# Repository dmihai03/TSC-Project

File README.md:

# eBook reader - Pacuraru Mihai Dorin

This product is an eBook reader that uses an **ESP32-C6** microcontroller powered by an **USB Type-C**.

 Implementation steps:
    - create 2D schematic
    - create 2D PCB, solving routing errors
    - add 3D model to every component 
    - pushed 2D PCB to 3D
    - created 3D model for battery
    - imported display model
    - build the final 3D model of product

---

## Block Diagram

---

## Hardware functionalities

### ESP32-C6 microcontroller

The ESP32-C6 microcontroller has a single core SoC RISC-V that supports:
  - WiFi6, Bluetooth 5, Zigbee and Thread
  - integrated flash memory up to 8 MB
  - 23 GPIO pins
  - SPI, 12C, UART, I2S, USB interfaces support

Charging and energy management:
  - USB-C that uses USB4110-GF-A connector with ESD protection for battery charging
  - LiPo battery that gets charged with the help of MCP73831 controller
  - the integrated circuit MAX17048G+T10 for monitorizing battery charging level via I2C interface

Display system:
  - E-Paper driver interface connected to microcontroller via SPI

Memory:
  - microSD card interface connected via SPI for heavy data

Buttons:
  - BOOT -> the microcontroller enters in bootloader
  - RESET -> general reset
  - I/O CHANGE -> user I/O interactions

### ESP32-C6 pins configuration
| Component | PIN |
|----|----|
|Display SPI | MOSI, CLK, CS, DC |
|BME688 | SDA, SCL, I2C |
|Buttons | GPIO1, GPIO2, GPIO3 |
|USB-C | D+, D-, VBUS |

---
## Bill of Materials (BOM)
| Component | Buy | Datasheet |
| ---------- | --------- | --------- |
| PFMF.050.1 | [Retailer](https://ro.mouser.com/ProductDetail/Schurter/PFMF.050.2?qs=1auRipcfynCums5v1iucSA%3D%3D) |  [Datasheet](https://ro.mouser.com/datasheet/2/358/typ_PFMF-1275918.pdf) |
| USB4110-GF-A | [Retailer](https://ro.mouser.com/ProductDetail/GCT/USB4110-GF-A?qs=KUoIvG%2F9IlYiZvIXQjyJeA%3D%3D) | [Datasheet](https://ro.mouser.com/datasheet/2/837/GCT_USB4110_Product_Drawing___20k_cycles-3455479.pdf) |
| USBLC6-2SC6Y | [Retailer](https://ro.mouser.com/ProductDetail/STMicroelectronics/USBLC6-2SC6Y?qs=gNDSiZmRJS%2FOgDexvXkdow%3D%3D) | [Datasheet](https://ro.mouser.com/datasheet/2/389/usblc6_2sc6y-1852505.pdf) |
| SD0805S020S1R0 | [Retailer](https://ro.mouser.com/ProductDetail/KYOCERA-AVX/SD0805S020S1R0?qs=jCA%252BPfw4LHbpkAoSnwrdjw%3D%3D) | [Datasheet](https://ro.mouser.com/datasheet/2/40/schottky-3165252.pdf) |
| DMG2305UX-7 | [Retailer](https://ro.mouser.com/ProductDetail/Diodes-Incorporated/DMG2305UX-7?qs=L1DZKBg7t5F%2FNBHrjfxC%252Bg%3D%3D) | [Datasheet](https://www.diodes.com/assets/Datasheets/DMG2305UX.pdf) |
| XC6220A331MR-G | [Retailer](https://ro.mouser.com/ProductDetail/Torex-Semiconductor/XC6220A331MR-G?qs=AsjdqWjXhJ8ZSWznL1J0gg%3D%3D) | [Datasheet](https://ro.mouser.com/datasheet/2/760/xc6220-3371556.pdf) |
| Condensator 100 uF TANT | [Retailer](https://ro.mouser.com/ProductDetail/KYOCERA-AVX/TAJW107M010RNJ?qs=Wtp%252Bf%2FAeVqIH8v1VxV%252B1Rg%3D%3D) | [Datasheet](https://ro.mouser.com/datasheet/2/40/TAJ-3165264.pdf) |
| 112A-TAAR-R03_ATTEND | [Retailer](https://www.digikey.ro/en/products/detail/attend-technology/112A-TAAR-R03/17633923) | [Datasheet](https://www.attend.com.tw/data/download/file/112A-TAAR-R03_Spec.pdf)
| ESP32-C6-WROOM-1-N8 | [Retailer](https://ro.mouser.com/ProductDetail/Espressif-Systems/ESP32-C6-WROOM-1-N8?qs=8Wlm6%252BaMh8ST02Gmwp74cw%3D%3D) | [Datasheet](https://ro.mouser.com/datasheet/2/891/Espressif_ESP32_C6_WROOM_1__Datasheet_V0_1_PRELIMI-3239987.pdf) |
| MCP73831 | [Retailer](https://ro.mouser.com/ProductDetail/Microchip-Technology/MCP73831T-2ACI-OT?qs=yUQqVecv4qvbBQBGbHx0Mw%3D%3D) | [Datasheet](https://ro.mouser.com/datasheet/2/268/MCP73831_Family_Data_Sheet_DS20001984H-3441711.pdf) |
| CHG_LED | [Retailer](https://store.comet.srl.ro/Catalogue/Product/40478/) | [Datasheet](https://www.snapeda.com/parts/KP-1608SURCK/Kingbright/datasheet/) |
| SI1308EDL-T1-GE3 | [Retailer](https://ro.mouser.com/ProductDetail/Vishay-Semiconductors/SI1308EDL-T1-GE3?qs=bX1%252BNvsK%2FBramh9tgpOaEw%3D%3D) | [Datasheet](https://www.vishay.com/doc?63399) |
| MBR0530 | [Retailer](https://ro.mouser.com/ProductDetail/Micro-Commercial-Components-MCC/MBR0530-T?qs=9VyI4qLX4NTSXkb9ynzJnA%3D%3D) | [Datasheet](https://ro.mouser.com/datasheet/2/258/mcc_mbr0520~mbr0560sod123-1179695.pdf) |
| L1 | [Retailer](https://ro.mouser.com/ProductDetail/Wurth-Elektronik/744043680?qs=PGXP4M47uW6VkZq%252BkzjrHA%3D%3D) | [Datasheet](https://www.we-online.com/components/products/datasheet/744043680.pdf) |
| FH34SRJ-24S-0.5SH_99_ | [Retailer](https://ro.mouser.com/ProductDetail/Hirose-Connector/FH34SRJ-24S-0.5SH99?qs=vcbW%252B4%252BSTIpKBl5ap9J8Fw%3D%3D) | [Datasheet](https://ro.mouser.com/datasheet/2/185/FH34SRJ_24S_0_5SH_99__CL0580_1255_6_99_2DDrawing_0-1615044.pdf) |
| BME688 | [Retailer](https://ro.mouser.com/ProductDetail/Bosch-Sensortec/BME688?qs=IS%252B4QmGtzzqQoVDscqwx3A%3D%3D) | [Datasheet](https://ro.mouser.com/datasheet/2/783/bst_bme688_fl000-2307034.pdf) |
| BD5229G-TR | [Retailer](https://ro.mouser.com/ProductDetail/ROHM-Semiconductor/BD5229G-TR?qs=4kLU8WoGk0vvnhrrYwdszw%3D%3D) | [Datasheet](https://fscdn.rohm.com/en/products/databook/datasheet/ic/power/voltage_detector/bd52xxg-e.pdf) |
| Button | [Retailer](https://ro.mouser.com/ProductDetail/CK/KMR221GULCLFS?qs=u2NJ%252B70r0goBXaNk7IrU0Q%3D%3D) | [Datasheet](https://www.ckswitches.com/media/1479/kmr2.pdf) |
| MAX17048G+T10 | [Retailer](https://ro.mouser.com/ProductDetail/Analog-Devices-Maxim-Integrated/MAX17048G%2bT10?qs=D7PJwyCwLAoGnnn8jEPRBQ%3D%3D) | [Datasheet](https://ro.mouser.com/datasheet/2/609/MAX17048_MAX17049-3469099.pdf) |
| W25Q512JVEIQ | [Retailer](https://ro.mouser.com/ProductDetail/Winbond/W25Q512JVEIQ?qs=l7cgNqFNU1jw6svr3at6tA%3D%3D) | [Datasheet](https://ro.mouser.com/datasheet/2/949/Winbond_W25Q512JV_Datasheet-3240039.pdf) |
| PGB1010603MR | [Retailer](https://ro.mouser.com/ProductDetail/Littelfuse/PGB1010603MRHF?qs=KvZd0dN2Zg%2FuIq6icj%252BGKA%3D%3D) | [Datasheet](https://www.littelfuse.com/media?resourcetype=datasheets&itemid=8a337998-d54d-466b-be4e-dc5bcd1f9321&filename=littelfuse_pulseguard_pgb1_datasheet.pdf) |
| QWIIC_RIGHT_ANGLE | [Retailer](https://ro.mouser.com/ProductDetail/GCT/USB4110-GF-A?qs=KUoIvG%2F9IlYiZvIXQjyJeA%3D%3D) | [Datasheet](https://ro.mouser.com/datasheet/2/837/GCT_USB4110_Product_Drawing___20k_cycles-3455479.pdf) |
| DS3231SN# | [Retailer](https://ro.mouser.com/ProductDetail/Analog-Devices-Maxim-Integrated/DS3231SN?qs=ffX8NcjNb2RmKAb9wAk9Ug%3D%3D) | [Datasheet](https://ro.mouser.com/datasheet/2/609/DS3231-3421123.pdf) |
| CPH3225A C10_SUPERCAP | [Retailer](https://ro.mouser.com/ProductDetail/Seiko-Semiconductors/CPH3225A?qs=3etwrb1wR%252BhUOph6lAO7eg%3D%3D) | [Datasheet](https://ro.mouser.com/datasheet/2/360/Seiko_Instruments_MicroBattery_E_20230330_2024Jan_-3561061.pdf) |
| Condensator 100nF | [Retailer](https://ro.mouser.com/ProductDetail/KYOCERA-AVX/06033G104ZAT2A?qs=NXubJDmysXJMPmHfVo6Z%252BA%3D%3D) | [Datasheet](https://ro.mouser.com/datasheet/2/40/KGM_Y5V-3223189.pdf) |
| Condensator 4.7uF | [Retailer](https://ro.mouser.com/ProductDetail/KYOCERA-AVX/0402ZD475MAT2A?qs=NBFAU1oqP4W4U2PCPHI0sg%3D%3D) | [Datasheet](https://ro.mouser.com/datasheet/2/40/cx5r_KGM-3223198.pdf) |
| Condensator 10uF | [Retailer](https://ro.mouser.com/ProductDetail/Samsung-Electro-Mechanics/CL10A106KQ8NNNL?qs=xZ%2FP%252Ba9zWqaes9JKSsob2Q%3D%3D) | [Datasheet](https://ro.mouser.com/datasheet/2/585/MLCC-1837944.pdf) |
| Condensator 1uF/50V | [Retailer](https://ro.mouser.com/ProductDetail/KYOCERA-AVX/06035D105MAT2A?qs=k4kUdCzLgS5%252BURKe1SOIeQ%3D%3D) | [Datasheet](https://ro.mouser.com/datasheet/2/40/cx5r_KGM-3223198.pdf) |
| Resistor 10K | [Retailer](https://ro.mouser.com/ProductDetail/Vishay-Beyschlag/MCS0402MD1002BE000?qs=17u8i%2FzlE8%2F9BrAaXkMk1w%3D%3D) | [Datasheet](https://www.vishay.com/doc?28952) |
| Resistor 200 | [Retailer](https://ro.mouser.com/ProductDetail/Vishay-Beyschlag/MCS0402MD2000BE100?qs=3SvaY9RawMJNVte4F12%252BZQ%3D%3D) | [Datasheet](https://www.vishay.com/doc?28952) |
| Resistor 100K | [Retailer](https://ro.mouser.com/ProductDetail/Vishay-Beyschlag/MCT0603PD1003DP500?qs=5aG0NVq1C4wWAn8Ei3OpZA%3D%3D) | [Datasheet](https://www.vishay.com/doc?28916) |
| Resistor 2.2 | [Retailer](https://ro.mouser.com/ProductDetail/SEI-Stackpole/RMCF0402FT2R20?qs=IPgv5n7u5QbBgyl0jwhwsA%3D%3D) | [Datasheet](https://ro.mouser.com/datasheet/2/385/SEI_RMCF_RMCP-3077565.pdf) |
| Resistor 5K1| [Retailer](https://www.venkel.com/part/TFCR0603-16W-K-5690FT) | [Datasheet](https://data.venkel.com/documents/tfcr-series?_gl=1*tdo8m*_ga*NTA1MTc5MTcyLjE3NDM4OTMzNjc.*_ga_JRKGBZNVM8*MTc0Mzg5MzM2Ni4xLjAuMTc0Mzg5MzM2OC41OC4wLjA.) |
| Resistor 2K | [Retailer](https://ro.mouser.com/ProductDetail/Vishay-Beyschlag/MCS04020C2001FE000?qs=wTZ%2FFzl837YG0wIkZJJOwQ%3D%3D) | [Datasheet](https://www.vishay.com/doc?28705) |
| Resistor 0.47 | [Retailer](https://ro.mouser.com/ProductDetail/SEI-Stackpole/CSR0402JKR470?qs=IPgv5n7u5QawIB6nBEt8wA%3D%3D) | [Datasheet](https://ro.mouser.com/datasheet/2/385/SEI_CSR_CSRN-3077593.pdf) |
| Resistor 15 | [Retailer](https://ro.mouser.com/ProductDetail/YAGEO/RT0402FRE0715RL?qs=BXCcY9r%252B08DFFpLSkPOIqQ%3D%3D) | [Datasheet](https://ro.mouser.com/datasheet/2/447/PYu_RT_1_to_0_01_RoHS_L_15-3461507.pdf) |

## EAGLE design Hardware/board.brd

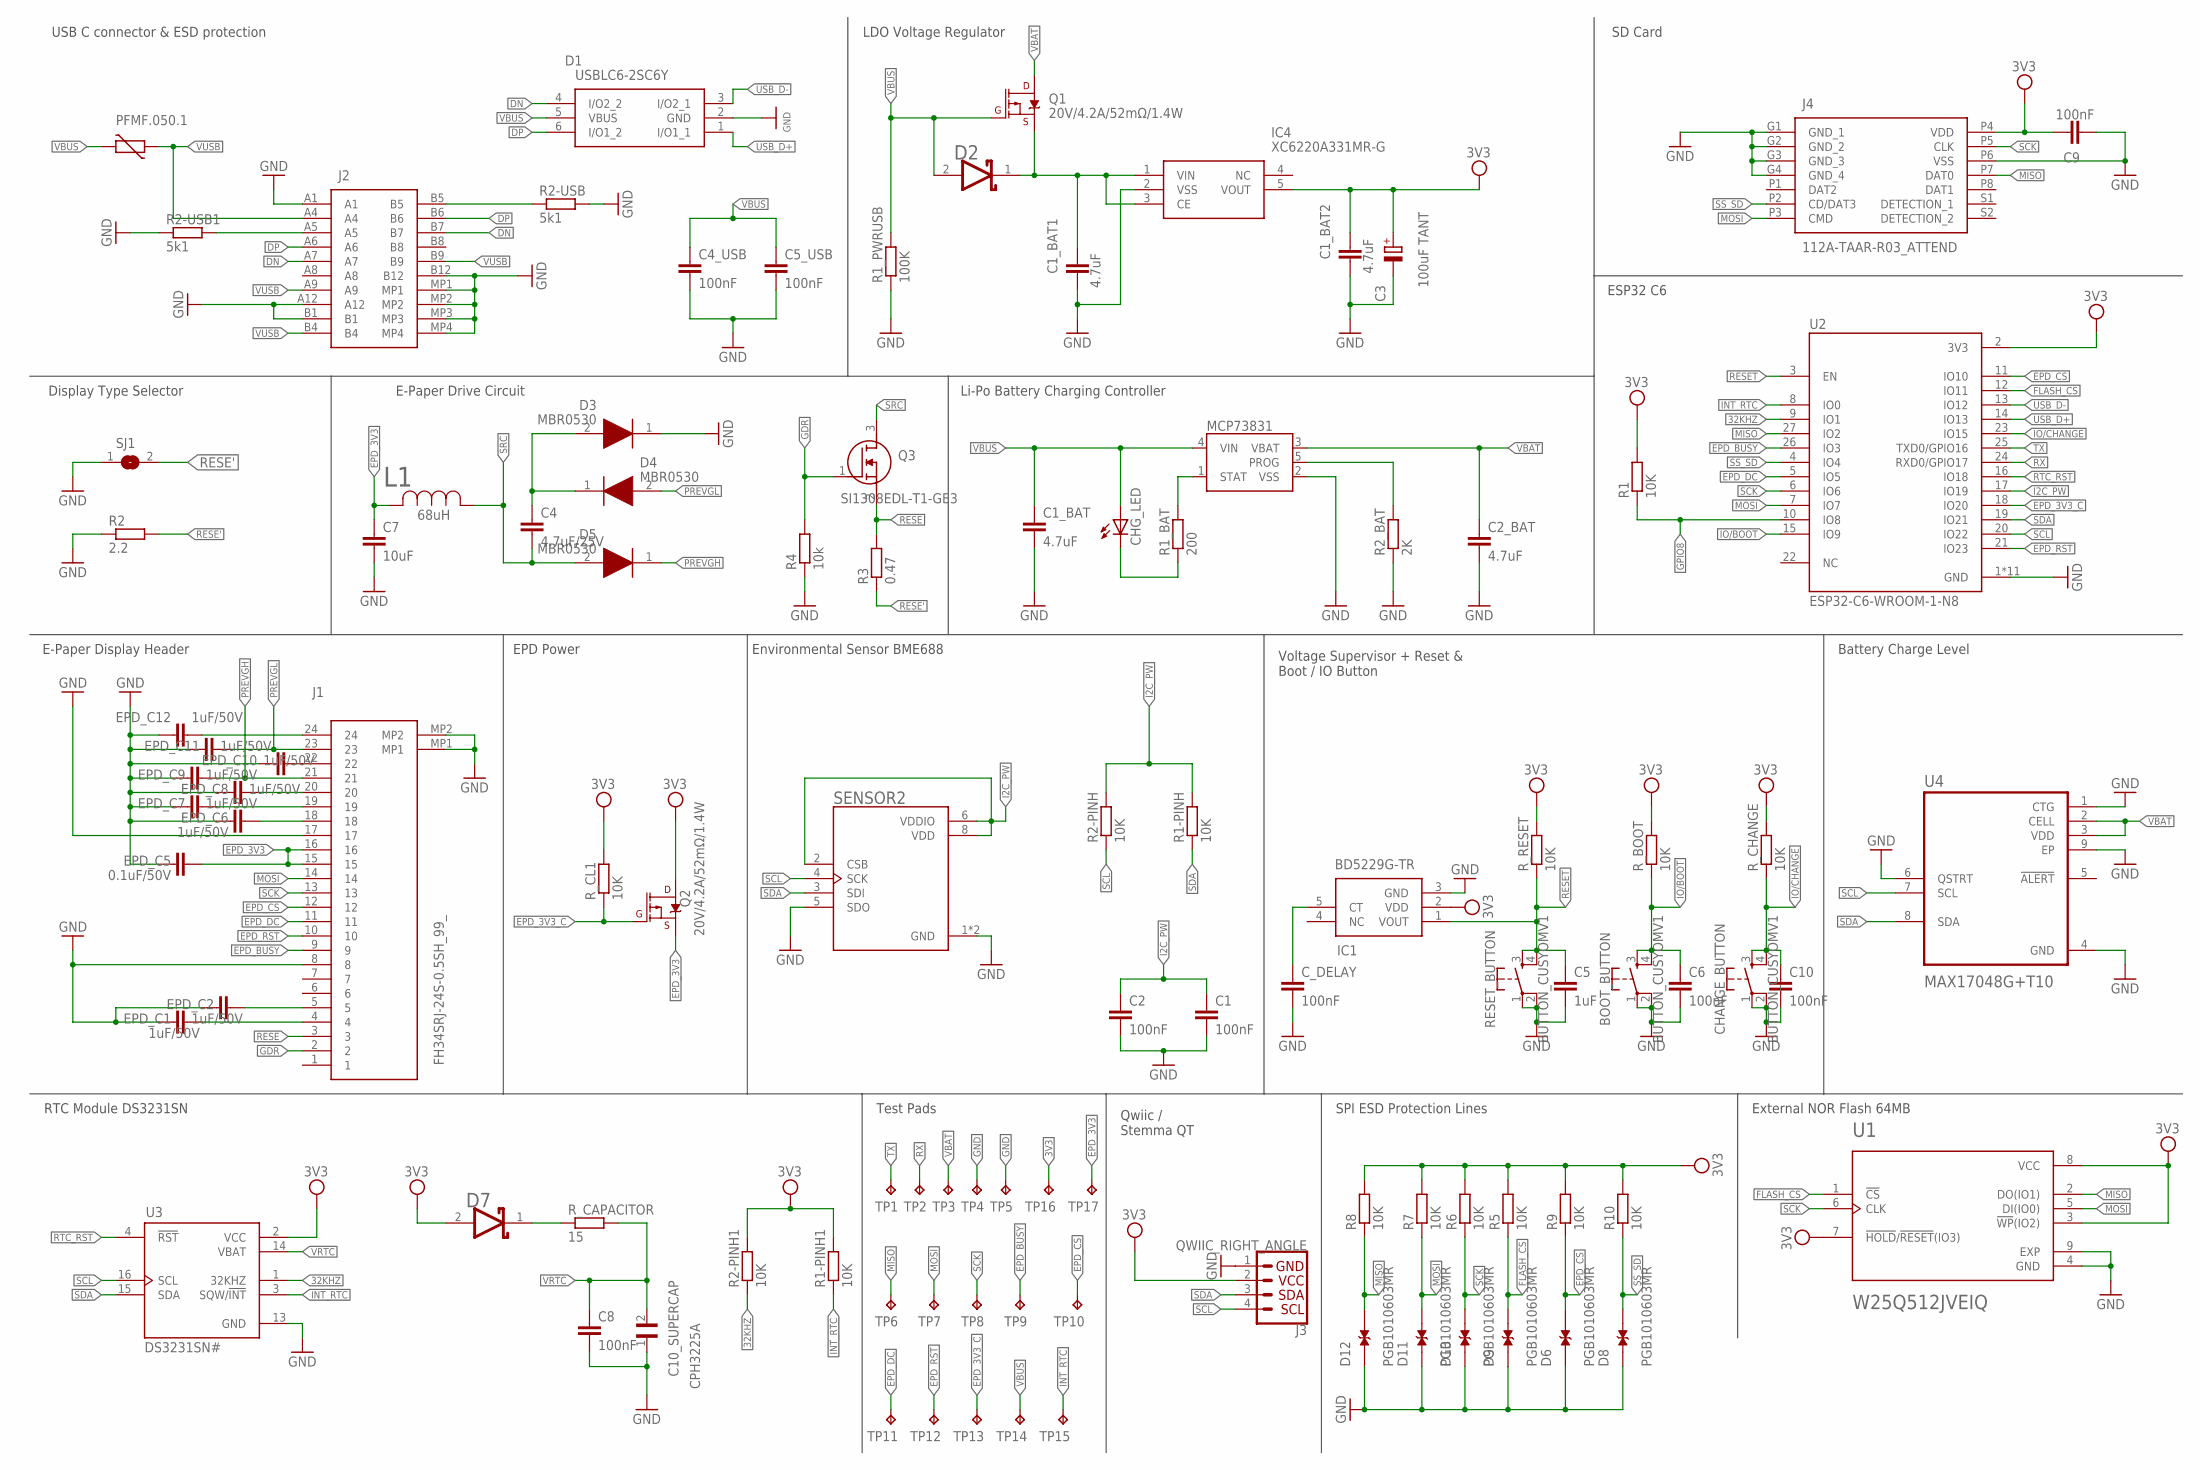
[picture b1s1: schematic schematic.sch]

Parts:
BOOT_BUTTON: BUTTON_CUSYOMV1; MYBUTTON
C1, C2, C4_USB, C5_USB, C6, C8, C9, C10: 100nF; ESP32_WROVER_EAGLE-LTSPICE_C0402
C1_BAT, C1_BAT1, C1_BAT2, C2_BAT: 4.7uF; ESP32_WROVER_EAGLE-LTSPICE_C0402
C3: 100uF TANT; RCL_CT3528
C4: 4.7uF/25V; ESP32_WROVER_EAGLE-LTSPICE_C0402
C5: 1uF; ESP32_WROVER_EAGLE-LTSPICE_C0402
C7: 10uF; ESP32_WROVER_EAGLE-LTSPICE_C0402
C10_SUPERCAP: CPH3225A; CAPCP3225X100N
CHANGE_BUTTON: BUTTON_CUSYOMV1; MYBUTTON
CHG_LED: ADAFRUIT_LEDCHIP-LED0603; ADAFRUIT_CHIP-LED0603
C_DELAY: 100nF; ESP32_WROVER_EAGLE-LTSPICE_C0402
D1: USBLC6-2SC6Y; SOT95P280X145-6N
D2, D7: ESP32_WROVER_AVX---SD0805S020S1R0_AVX_SD0805S020S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; ESP32_WROVER_AVX---SD0805S020S1R0_AVX_SD0805S020S1R0_0
D3, D4, D5: MBR0530; SOD3716X135N
D6, D8, D9, D10, D11, D12: PGB1010603MR; DIOC1608X36N
EPD_C1, EPD_C2, EPD_C6, EPD_C7, EPD_C8, EPD_C9, EPD_C10, EPD_C11, EPD_C12: 1uF/50V; ESP32_WROVER_EAGLE-LTSPICE_C0402
EPD_C5: 0.1uF/50V; ESP32_WROVER_EAGLE-LTSPICE_C0402
IC1: BD5229G-TR; SOT95P280X125-5N
IC4: XC6220A331MR-G; SOT95P280X120-5N
J1: FH34SRJ-24S-0.5SH_99_; FH34SRJ24S05SH99
J2: SAMACSYS_PARTS_USB4110-GF-A; SAMACSYS_PARTS_USB4110GFA
J3: QWIIC_RIGHT_ANGLE; JST04_1MM_RA
J4: 112A-TAAR-R03_ATTEND; 112ATAARR03ATTEND
L1: 744043680IND_4828-WE-TPC_WRE; IND_4828-WE-TPC_WRE
MCP73831: ESP32_WROVER_SPARKFUN-IC-POWER_MCP73831; ESP32_WROVER_SPARKFUN-IC-POWER_SOT23-5
PFMF.050.1: ESP32C6_VARISTORCN1812; ESP32C6_VARISTOR_CT/CN1812
Q1, Q2: 20V/4.2A/52mΩ/1.4W; ESP32_WROVER_SPARKFUN-DISCRETESEMI_SOT23-3
Q3: SI1308EDL-T1-GE3; SOT65P210X110-3N
R1, R1-PINH, R1-PINH1, R2-PINH, R2-PINH1, R5, R6, R7, R8, R9, R10: 10K; ESP32_WROVER_EAGLE-LTSPICE_R0402
R1_BAT: 200; ESP32_WROVER_EAGLE-LTSPICE_R0402
R1_PWRUSB: 100K; ESP32_WROVER_EAGLE-LTSPICE_R0402
R2: 2.2; ESP32_WROVER_EAGLE-LTSPICE_R0402
R2-USB, R2-USB1: 5k1; ESP32_WROVER_EAGLE-LTSPICE_R0402
R2_BAT: 2K; ESP32_WROVER_EAGLE-LTSPICE_R0402
R3: 0.47; ESP32_WROVER_EAGLE-LTSPICE_R0402
R4: 10k; ESP32_WROVER_EAGLE-LTSPICE_R0402
RESET_BUTTON: BUTTON_CUSYOMV1; MYBUTTON
R_BOOT: 10K; ESP32_WROVER_EAGLE-LTSPICE_R0402
R_CAPACITOR: 15; ESP32_WROVER_EAGLE-LTSPICE_R0402
R_CHANGE: 10K; ESP32_WROVER_EAGLE-LTSPICE_R0402
R_CL1: 10K; ESP32_WROVER_EAGLE-LTSPICE_R0402
R_RESET: 10K; ESP32_WROVER_EAGLE-LTSPICE_R0402
SENSOR2: ESP32_WROVER_BME680_BME680; ESP32_WROVER_BME680_PSON80P300X300X100-8N
SJ1: SJ
TP1, TP2, TP3, TP4, TP5, TP6, TP7, TP8, TP9, TP10, TP11, TP12, TP13, TP14, TP15, TP16, TP17: TPTP20R; TP20R
U1: W25Q512JVEIQ; SON127P600X800X80-9N
U2: ESP32-C6-WROOM-1-N8; XCVR_ESP32-C6-WROOM-1-N8
U3: DS3231SN#; SOIC127P1032X265-16N
U4: MAX17048G+T10; SON50P200X200X80-9N

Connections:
3V3: C1_BAT2.1, C3.+, C9.1, D7.2 (ANODE), IC1.2 (VDD), IC4.5 (VOUT), J3.2, J4.P4 (VDD), Q2.3 (D), R1.2, R1-PINH1.2, R2-PINH1.2, R5.2, R6.2, R7.2, R8.2, R9.2, R10.2, R_BOOT.2, R_CHANGE.2, R_CL1.2, R_RESET.2, TP16.TP, U1.3 (!WP!(IO2)), U1.7 (!HOLD!/!RESET!(IO3)), U1.8 (VCC), U2.2 (3V3), U3.2 (VCC)
32KHZ: R2-PINH1.1, U2.9 (IO1), U3.1 (32KHZ)
DN: D1.4 (I/O2_2), J2.A7, J2.B7
DP: D1.6 (I/O1_2), J2.A6, J2.B6
EPD_3V3: C7.1, EPD_C5.2, J1.15, J1.16, L1.2, Q2.2 (S), TP17.TP
EPD_3V3_C: Q2.1 (G), R_CL1.1, TP13.TP, U2.18 (IO20)
EPD_BUSY: J1.9, TP9.TP, U2.26 (IO3)
EPD_CS: D6.2, J1.12, R9.1, TP10.TP, U2.11 (IO10)
EPD_DC: J1.11, TP11.TP, U2.5 (IO5)
EPD_RST: J1.10, TP12.TP, U2.21 (IO23)
FLASH_CS: D9.2, R5.1, U1.1 (!CS), U2.12 (IO11)
GDR: J1.2, Q3.1 (G), R4.2
GND: BOOT_BUTTON.1, BOOT_BUTTON.2, C1.2, C1_BAT.2, C1_BAT1.2, C1_BAT2.2, C2.2, C2_BAT.2, C3.-, C4_USB.2, C5.2, C5_USB.2, C6.2, C7.2, C8.2, C9.2, C10.2, C10_SUPERCAP.1, CHANGE_BUTTON.1, CHANGE_BUTTON.2, C_DELAY.2, D1.2 (GND), D3.1 (K), D6.1, D8.1, D9.1, D10.1, D11.1, D12.1, EPD_C1.1, EPD_C2.1, EPD_C5.1, EPD_C6.1, EPD_C7.1, EPD_C8.1, EPD_C9.1, EPD_C10.1, EPD_C11.1, EPD_C12.1, IC1.3 (GND), IC4.2 (VSS), J1.8, J1.17, J1.MP1, J1.MP2, J2.A1, J2.A12, J2.B1, J2.B12, J2.MP1, J2.MP2, J2.MP3, J2.MP4, J3.1, J4.G1 (GND_1), J4.G2 (GND_2), J4.G3 (GND_3), J4.G4 (GND_4), J4.P6 (VSS), MCP73831.2 (VSS), R1_PWRUSB.1, R2.1, R2-USB.2, R2-USB1.1, R2_BAT.1, R4.1, RESET_BUTTON.1, RESET_BUTTON.2, SENSOR2.1 (GND), SENSOR2.5 (SDO), SENSOR2.7 (GND), SJ1.1, TP4.TP, TP5.TP, U1.4 (GND), U1.9 (EXP), U2.1 (GND), U2.28 (GND), U2.29_1 (GND), U2.29_2 (GND), U2.29_3 (GND), U2.29_4 (GND), U2.29_5 (GND), U2.29_6 (GND), U2.29_7 (GND), U2.29_8 (GND), U2.29_9 (GND), U3.13 (GND), U4.1 (CTG), U4.4 (GND), U4.6 (QSTRT), U4.9 (EP)
GPIO8: R1.1, U2.10 (IO8)
I2C_PW: C1.1, C2.1, R1-PINH.2, R2-PINH.2, SENSOR2.2 (CSB), SENSOR2.6 (VDDIO), SENSOR2.8 (VDD), U2.17 (IO19)
INT_RTC: R1-PINH1.1, TP15.TP, U2.8 (IO0), U3.3 (SQW/!INT)
IO/BOOT: BOOT_BUTTON.3, BOOT_BUTTON.4, C6.1, R_BOOT.1, U2.15 (IO9)
IO/CHANGE: C10.1, CHANGE_BUTTON.3, CHANGE_BUTTON.4, R_CHANGE.1, U2.23 (IO15)
MISO: D12.2, J4.P7 (DAT0), R8.1, TP6.TP, U1.2 (DO(IO1)), U2.27 (IO2)
MOSI: D11.2, J1.14, J4.P3 (CMD), R7.1, TP7.TP, U1.5 (DI(IO0)), U2.7 (IO7)
unnamed: J2.A5, R2-USB1.2
unnamed: J2.B5, R2-USB.1
unnamed: C1_BAT1.1, D2.1 (CATHODE), IC4.1 (VIN), IC4.3 (CE), Q1.2 (S)
unnamed: MCP73831.5 (PROG), R2_BAT.2
unnamed: EPD_C2.2, J1.5
unnamed: EPD_C1.2, J1.4
unnamed: CHG_LED.C, R1_BAT.1
unnamed: MCP73831.1 (STAT), R1_BAT.2
unnamed: EPD_C12.2, J1.24
unnamed: C_DELAY.1, IC1.5 (CT)
unnamed: EPD_C10.2, J1.22
unnamed: C4.1, D3.2 (A), D4.1 (K)
unnamed: EPD_C8.2, J1.20
unnamed: EPD_C7.2, J1.19
unnamed: EPD_C6.2, J1.18
unnamed: D7.1 (CATHODE), R_CAPACITOR.1
PREVGH: D5.1 (K), EPD_C9.2, J1.21
PREVGL: D4.2 (A), EPD_C11.2, J1.23
RESE: J1.3, Q3.2 (S), R3.2
RESE': R2.2, R3.1, SJ1.2
RESET: C5.1, IC1.1 (VOUT), RESET_BUTTON.3, RESET_BUTTON.4, R_RESET.1, U2.3 (EN)
RTC_RST: U2.16 (IO18), U3.4 (!RST)
RX: TP2.TP, U2.24 (RXD0/GPIO17)
SCK: D10.2, J1.13, J4.P5 (CLK), R6.1, TP8.TP, U1.6 (CLK), U2.6 (IO6)
SCL: J3.4, R2-PINH.1, SENSOR2.4 (SCK), U2.20 (IO22), U3.16 (SCL), U4.7 (SCL)
SDA: J3.3, R1-PINH.1, SENSOR2.3 (SDI), U2.19 (IO21), U3.15 (SDA), U4.8 (SDA)
SRC: C4.2, D5.2 (A), L1.1, Q3.3 (D)
SS_SD: D8.2, J4.P2 (CD/DAT3), R10.1, U2.4 (IO4)
TX: TP1.TP, U2.25 (TXD0/GPIO16)
USB_D+: D1.1 (I/O1_1), U2.14 (IO13)
USB_D-: D1.3 (I/O2_1), U2.13 (IO12)
VBAT: C2_BAT.1, MCP73831.3 (VBAT), Q1.3 (D), TP3.TP, U4.2 (CELL), U4.3 (VDD)
VBUS: C1_BAT.1, C4_USB.1, C5_USB.1, CHG_LED.A, D1.5 (VBUS), D2.2 (ANODE), MCP73831.4 (VIN), PFMF.050.1.2, Q1.1 (G), R1_PWRUSB.2, TP14.TP
VRTC: C8.1, C10_SUPERCAP.2, R_CAPACITOR.2, U3.14 (VBAT)
VUSB: J2.A4, J2.A9, J2.B4, J2.B9, PFMF.050.1.1

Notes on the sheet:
USB C connector & ESD protection
LDO Voltage Regulator
SD Card
Display Type Selector
E-Paper Drive Circuit
Li-Po Battery Charging Controller
ESP32 C6
E-Paper Display Header
EPD Power
Environmental Sensor BME688
Voltage Supervisor + Reset & Boot / IO Button
Battery Charge Level
RTC Module DS3231SN
Test Pads
Qwiic / Stemma QT
SPI ESD Protection Lines
External NOR Flash 64MB

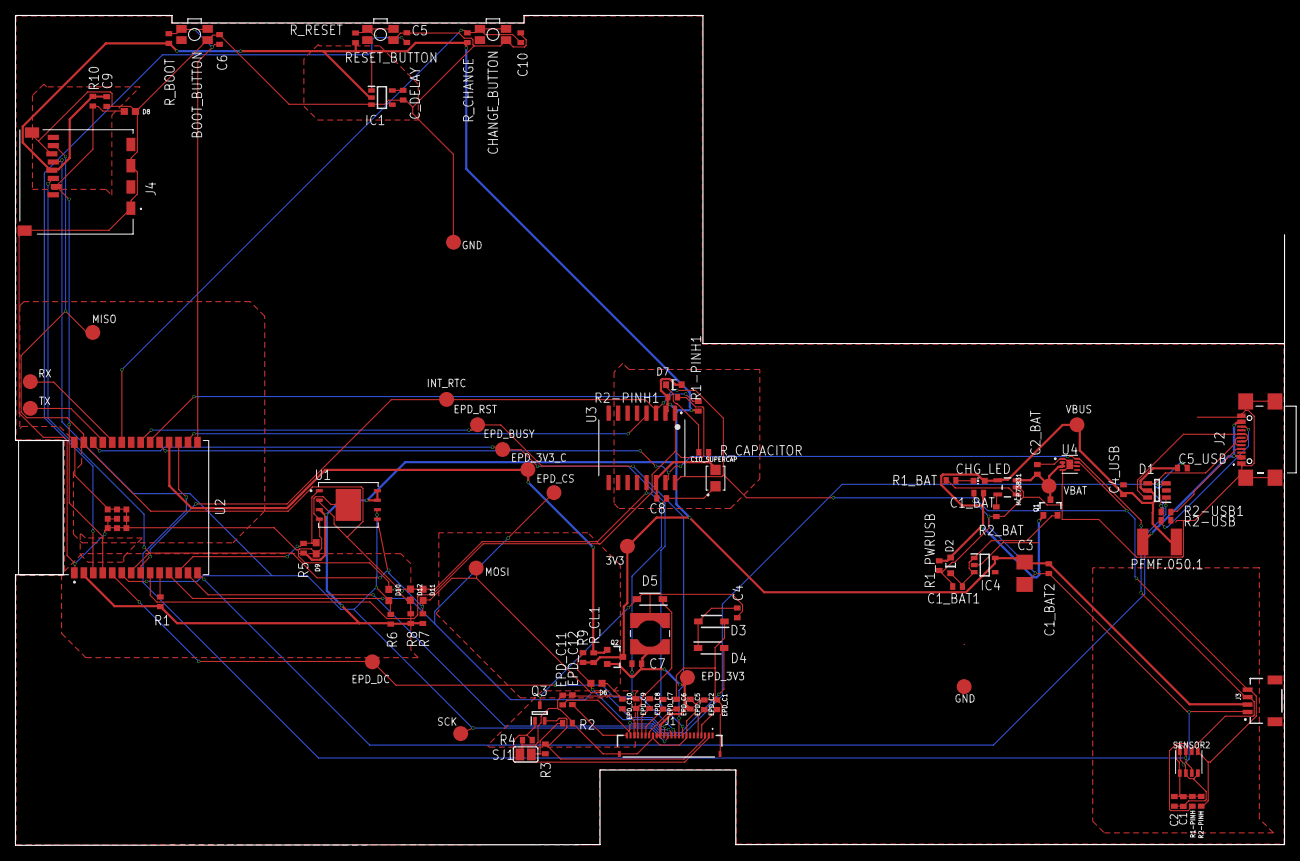
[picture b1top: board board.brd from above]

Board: 2 copper layers, 170.2 x 111.3 mm, 103 parts (0 on the bottom side), 55 nets.

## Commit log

2025-03-17 Create LICENSE
2025-03-17 Add skel
2025-03-29 Add schematic
2025-04-06 Finish first stage w/o additional assigments due to deadline delay
2025-04-06 Add second task
2025-04-06 Add schema bloc
2025-04-15 Fix issues

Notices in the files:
parts and their libraries:
COPYRIGHT: Copyright (C) 2024 Ultra Librarian. All rights reserved.
